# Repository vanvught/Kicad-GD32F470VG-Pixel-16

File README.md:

# Kicad GD32F470VG Pixel 16-ports x 4 Universes

Firmware [https://github.com/vanvught/GD32F470VG-Pixel-16-Ports](https://github.com/vanvught/GD32F470VG-Pixel-16-Ports)

More information [https://www.gd32-dmx.org/pixel.html](https://www.gd32-dmx.org/pixel.html)

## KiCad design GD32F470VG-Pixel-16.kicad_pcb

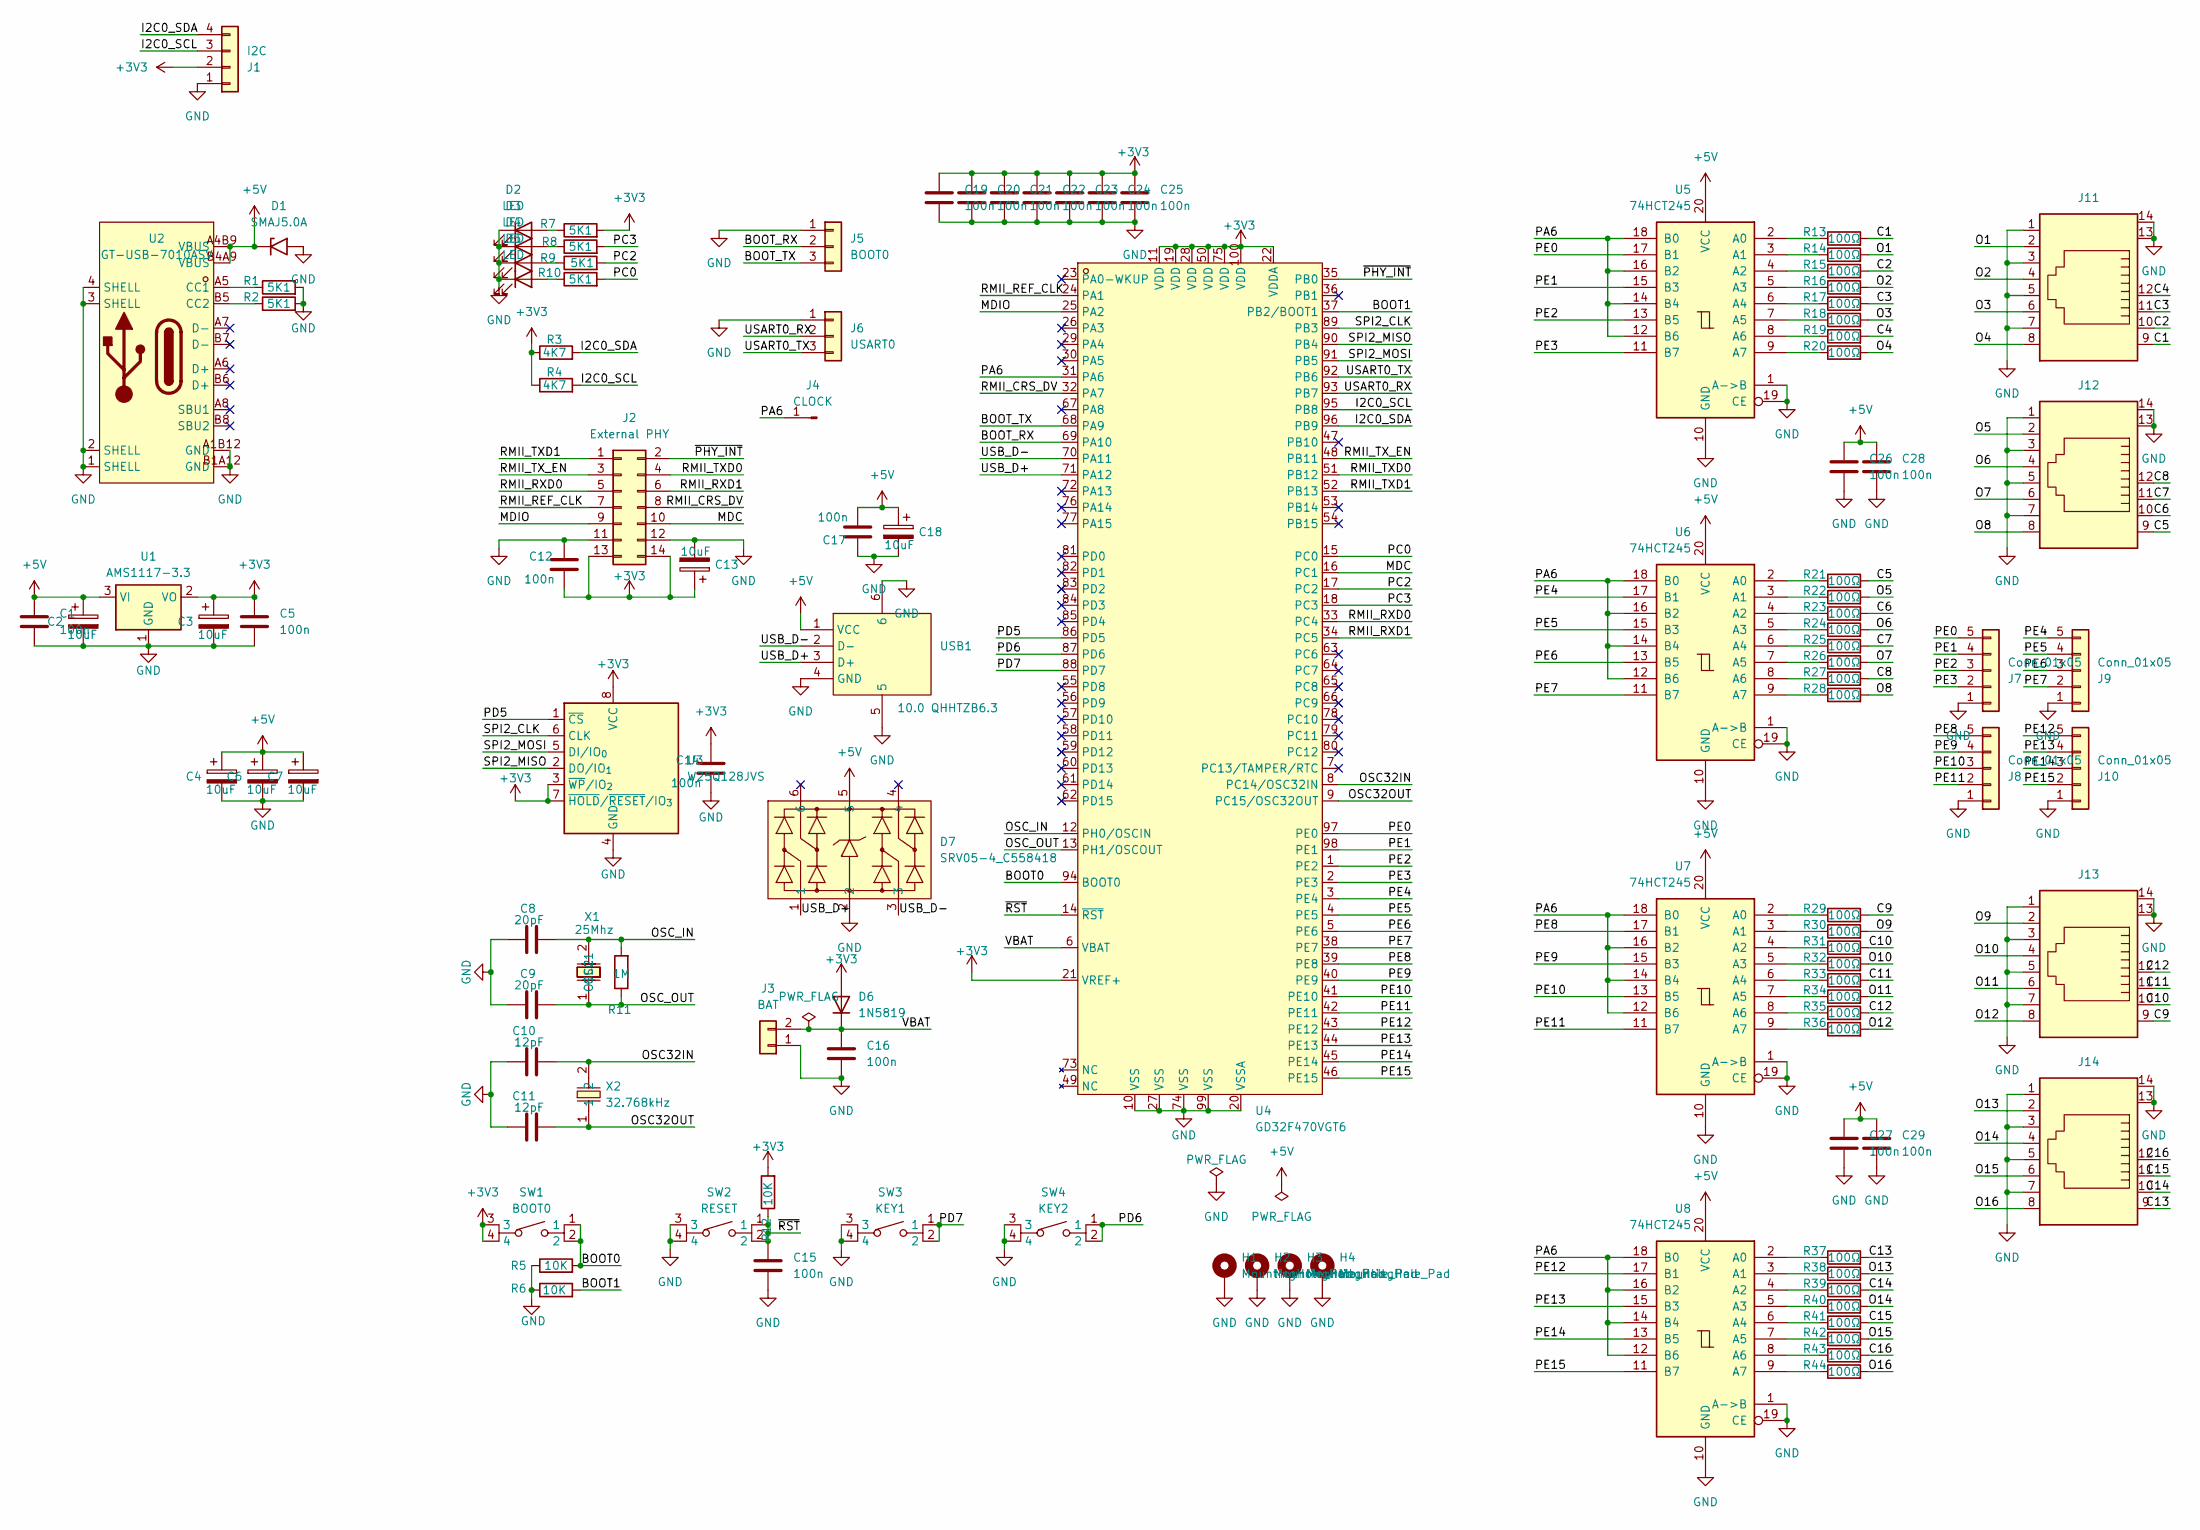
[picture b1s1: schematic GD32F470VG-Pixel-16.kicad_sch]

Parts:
C1, C5, C12, C14, C15, C16, C17, C19, C20, C21, C22, C23, C24, C25, C26, C27, C28, C29: 100n; C_0603_1608Metric; LCSC Part C14663
C2, C3, C4, C6, C7, C13, C18: 10uF; CP_EIA-3216-18_Kemet-A; LCSC Part C7171
C8, C9: 20pF; C_0603_1608Metric; LCSC Part C1648
C10, C11: 12pF; C_0603_1608Metric; LCSC Part C38523
D1: SMAJ5.0A; D_SMA; LCSC Part C113952
D2, D3, D4, D5: LED; LED_0805_2012Metric; LCSC Part C2297
D6: 1N5819; D_SOD-323; LCSC Part C48997863
D7: SRV05-4_C558418; SOT-23-6_L2.9-W1.6-P0.95-LS2.8-BL; MPN SRV05-4; LCSC Part C558418
H1, H2, H3, H4: MountingHole_Pad; MountingHole_2.7mm_M2.5_Pad
J1: I2C; PinHeader_1x04_P2.54mm_Vertical
J2: External PHY; PinSocket_2x07_P2.54mm_Horizontal
J3: BAT; PinHeader_1x02_P2.54mm_Vertical
J4: CLOCK; PinHeader_1x01_P2.54mm_Vertical
J5: BOOT0; PinHeader_1x03_P2.54mm_Vertical
J6: USART0; PinHeader_1x03_P2.54mm_Vertical
J7, J8, J9, J10: Conn_01x05; PinHeader_1x05_P2.54mm_Vertical
J11, J12, J13, J14: RJ45-with-additional-row
R1, R2, R7, R8, R9, R10: 5K1; R_0603_1608Metric; LCSC Part C23186
R3, R4: 4K7; R_0603_1608Metric; LCSC Part C23162
R5, R6, R12: 10K; R_0603_1608Metric; LCSC Part C25804
R11: 1M; R_0603_1608Metric; LCSC Part C22935
R13, R14, R15, R16, R17, R18, R19, R20, R21, R22, R23, R24, R25, R26, R27, R28, R29, R30, R31, R32, R33, R34, R35, R36, R37, R38, R39, R40, R41, R42, R43, R44: 100Ω; R_0603_1608Metric; LCSC Part C22775
SW1: BOOT0; KEY-SMD_4P-L6.0-W6.0-P4.50-LS9.0; MPN PTS645SM43SMTR92LFS; LCSC Part C221880
SW2: RESET; KEY-SMD_4P-L6.0-W6.0-P4.50-LS9.0; MPN PTS645SM43SMTR92LFS; LCSC Part C221880
SW3: KEY1; KEY-SMD_4P-L6.0-W6.0-P4.50-LS9.0; MPN PTS645SM43SMTR92LFS; LCSC Part C221880
SW4: KEY2; KEY-SMD_4P-L6.0-W6.0-P4.50-LS9.0; MPN PTS645SM43SMTR92LFS; LCSC Part C221880
U1: AMS1117-3.3; SOT-223-3_TabPin2
U2: GT-USB-7010ASV; USB-C-SMD_G-SWITCH_GT-USB-7010ASV; MPN GT-USB-7010ASV; LCSC Part C2988369
U3: W25Q128JVS; SOIC-8_5.3x5.3mm_P1.27mm; LCSC Part C97521
U4: GD32F470VGT6; LQFP-100_L14.0-W14.0-P0.50-LS16.0-BL; MPN GD32F470VGT6; LCSC Part C3029773
U5, U6, U7, U8: 74HCT245; SOIC-20W_7.5x12.8mm_P1.27mm; LCSC Part C5979
USB1: 10.0 QHHTZB6.3; USB-A-TH_10.0QHHTZB6.3; MPN 10.0 QHHTZB6.3; LCSC Part C668591
X1: 25Mhz; HC-49S_L11.4-W4.8; MPN X49SM25MSD2SC; LCSC Part C14872
X2: 32.768kHz; FC-135R_L3.2-W1.5; MPN Q13FC13500004; LCSC Part C32346

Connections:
+3V3: C3.1, C5.1, C12.2, C13.1, C14.1, C19.1, C20.1, C21.1, C22.1, C23.1, C24.1, C25.1, D6.2 (A), J1.2, J2.13, J2.14, R3.1, R4.1, R7.2, R12.2, SW1.3, SW1.4, U1.2 (VO), U3.3 (~WP/IO_{2}), U3.7 (~HOLD/~RESET/IO_{3}), U3.8 (VCC), U4.11 (VDD), U4.19 (VDD), U4.21 (VREF+), U4.22 (VDDA), U4.28 (VDD), U4.50 (VDD), U4.75 (VDD), U4.100 (VDD)
+5V: C1.1, C2.1, C4.1, C6.1, C7.1, C17.2, C18.1, C26.1, C27.1, C28.1, C29.1, D1.1 (A1), D7.5, U1.3 (VI), U2.A4B9 (VBUS), U2.B4A9 (VBUS), U5.20 (VCC), U6.20 (VCC), U7.20 (VCC), U8.20 (VCC), USB1.1 (VCC)
/BOOT0: R5.2, SW1.1, SW1.2, U4.94 (BOOT0)
/BOOT1: R6.2, U4.37 (PB2/BOOT1)
/BOOT_RX: J5.2, U4.69 (PA10)
/BOOT_TX: J5.3, U4.68 (PA9)
/C1: J11.9, R13.2
/C2: J11.10, R15.2
/C3: J11.11, R17.2
/C4: J11.12, R19.2
/C5: J12.9, R21.2
/C6: J12.10, R23.2
/C7: J12.11, R25.2
/C8: J12.12, R27.2
/C9: J13.9, R29.2
/C10: J13.10, R31.2
/C11: J13.11, R33.2
/C12: J13.12, R35.2
/C13: J14.9, R37.2
/C14: J14.10, R39.2
/C15: J14.11, R41.2
/C16: J14.12, R43.2
/I2C0_SCL: J1.3, R4.2, U4.95 (PB8)
/I2C0_SDA: J1.4, R3.2, U4.96 (PB9)
/MDC: J2.10, U4.16 (PC1)
/MDIO: J2.9, U4.25 (PA2)
/O1: J11.2, R14.2
/O2: J11.4, R16.2
/O3: J11.6, R18.2
/O4: J11.8, R20.2
/O5: J12.2, R22.2
/O6: J12.4, R24.2
/O7: J12.6, R26.2
/O8: J12.8, R28.2
/O9: J13.2, R30.2
/O10: J13.4, R32.2
/O11: J13.6, R34.2
/O12: J13.8, R36.2
/O13: J14.2, R38.2
/O14: J14.4, R40.2
/O15: J14.6, R42.2
/O16: J14.8, R44.2
/OSC32IN: C10.2, U4.8 (PC14/OSC32IN), X2.2
/OSC32OUT: C11.2, U4.9 (PC15/OSC32OUT), X2.1
/OSC_IN: C8.2, R11.2, U4.12 (PH0/OSCIN), X1.2 (OSC2)
/OSC_OUT: C9.2, R11.1, U4.13 (PH1/OSCOUT), X1.1 (OSC1)
/PA6: J4.1 (Pin_1_1), U4.31 (PA6), U5.12 (B6), U5.14 (B4), U5.16 (B2), U5.18 (B0), U6.12 (B6), U6.14 (B4), U6.16 (B2), U6.18 (B0), U7.12 (B6), U7.14 (B4), U7.16 (B2), U7.18 (B0), U8.12 (B6), U8.14 (B4), U8.16 (B2), U8.18 (B0)
/PC0: R10.2, U4.15 (PC0)
/PC2: R9.2, U4.17 (PC2)
/PC3: R8.2, U4.18 (PC3)
/PD5: U3.1 (~CS), U4.86 (PD5)
/PD6: SW4.1, SW4.2, U4.87 (PD6)
/PD7: SW3.1, SW3.2, U4.88 (PD7)
/PE0: J7.5, U4.97 (PE0), U5.17 (B1)
/PE1: J7.4, U4.98 (PE1), U5.15 (B3)
/PE2: J7.3, U4.1 (PE2), U5.13 (B5)
/PE3: J7.2, U4.2 (PE3), U5.11 (B7)
/PE4: J9.5, U4.3 (PE4), U6.17 (B1)
/PE5: J9.4, U4.4 (PE5), U6.15 (B3)
/PE6: J9.3, U4.5 (PE6), U6.13 (B5)
/PE7: J9.2, U4.38 (PE7), U6.11 (B7)
/PE8: J8.5, U4.39 (PE8), U7.17 (B1)
/PE9: J8.4, U4.40 (PE9), U7.15 (B3)
/PE10: J8.3, U4.41 (PE10), U7.13 (B5)
/PE11: J8.2, U4.42 (PE11), U7.11 (B7)
/PE12: J10.5, U4.43 (PE12), U8.17 (B1)
/PE13: J10.4, U4.44 (PE13), U8.15 (B3)
/PE14: J10.3, U4.45 (PE14), U8.13 (B5)
/PE15: J10.2, U4.46 (PE15), U8.11 (B7)
/RMII_CRS_DV: J2.8, U4.32 (PA7)
/RMII_REF_CLK: J2.7, U4.24 (PA1)
/RMII_RXD0: J2.5, U4.33 (PC4)
/RMII_RXD1: J2.6, U4.34 (PC5)
/RMII_TXD0: J2.4, U4.51 (PB12)
/RMII_TXD1: J2.1, U4.52 (PB13)
/RMII_TX_EN: J2.3, U4.48 (PB11)
/SPI2_CLK: U3.6 (CLK), U4.89 (PB3)
/SPI2_MISO: U3.2 (DO/IO_{1}), U4.90 (PB4)
/SPI2_MOSI: U3.5 (DI/IO_{0}), U4.91 (PB5)
/USART0_RX: J6.2, U4.93 (PB7)
/USART0_TX: J6.3, U4.92 (PB6)
/USB_D+: D7.1, U4.71 (PA12), USB1.3 (D+)
/USB_D-: D7.3, U4.70 (PA11), USB1.2 (D-)
/VBAT: C16.1, D6.1 (K), J3.2, U4.6 (VBAT)
/~PHY_INT: J2.2, U4.35 (PB0)
/~RST: C15.1, R12.1, SW2.1, SW2.2, U4.14 (~RST)
GND: C1.2, C2.2, C3.2, C4.2, C5.2, C6.2, C7.2, C8.1, C9.1, C10.1, C11.1, C12.1, C13.2, C14.2, C15.2, C16.2, C17.1, C18.2, C19.2, C20.2, C21.2, C22.2, C23.2, C24.2, C25.2, C26.2, C27.2, C28.2, C29.2, D1.2 (A2), D2.1 (K), D3.1 (K), D4.1 (K), D5.1 (K), D7.2, H1.1 (1_1), H2.1 (1_1), H3.1 (1_1), H4.1 (1_1), J1.1, J2.11, J2.12, J3.1, J5.1, J6.1, J7.1, J8.1, J9.1, J10.1, J11.1, J11.3, J11.5, J11.7, J11.13, J11.14, J12.1, J12.3, J12.5, J12.7, J12.13, J12.14, J13.1, J13.3, J13.5, J13.7, J13.13, J13.14, J14.1, J14.3, J14.5, J14.7, J14.13, J14.14, R1.2, R2.2, R5.1, R6.1, SW2.3, SW2.4, SW3.3, SW3.4, SW4.3, SW4.4, U1.1 (GND), U2.1 (SHELL), U2.2 (SHELL), U2.3 (SHELL), U2.4 (SHELL), U2.A1B12 (GND), U2.B1A12 (GND), U3.4 (GND), U4.10 (VSS), U4.20 (VSSA), U4.27 (VSS), U4.74 (VSS), U4.99 (VSS), U5.1 (A->B), U5.10 (GND), U5.19 (CE), U6.1 (A->B), U6.10 (GND), U6.19 (CE), U7.1 (A->B), U7.10 (GND), U7.19 (CE), U8.1 (A->B), U8.10 (GND), U8.19 (CE), USB1.4 (GND), USB1.5, USB1.6
unnamed: D2.2 (A), R7.1
unnamed: D3.2 (A), R8.1
unnamed: D4.2 (A), R9.1
unnamed: D5.2 (A), R10.1
unnamed: R1.1, U2.A5 (CC1)
unnamed: R2.1, U2.B5 (CC2)
unnamed: R13.1, U5.2 (A0)
unnamed: R14.1, U5.3 (A1)
unnamed: R15.1, U5.4 (A2)
unnamed: R16.1, U5.5 (A3)
unnamed: R17.1, U5.6 (A4)
unnamed: R18.1, U5.7 (A5)
unnamed: R19.1, U5.8 (A6)
unnamed: R20.1, U5.9 (A7)
unnamed: R21.1, U6.2 (A0)
unnamed: R22.1, U6.3 (A1)
unnamed: R23.1, U6.4 (A2)
unnamed: R24.1, U6.5 (A3)
unnamed: R25.1, U6.6 (A4)
unnamed: R26.1, U6.7 (A5)
unnamed: R27.1, U6.8 (A6)
unnamed: R28.1, U6.9 (A7)
unnamed: R29.1, U7.2 (A0)
unnamed: R30.1, U7.3 (A1)
unnamed: R31.1, U7.4 (A2)
unnamed: R32.1, U7.5 (A3)
unnamed: R33.1, U7.6 (A4)
unnamed: R34.1, U7.7 (A5)
unnamed: R35.1, U7.8 (A6)
unnamed: R36.1, U7.9 (A7)
unnamed: R37.1, U8.2 (A0)
unnamed: R38.1, U8.3 (A1)
unnamed: R39.1, U8.4 (A2)
unnamed: R40.1, U8.5 (A3)
unnamed: R41.1, U8.6 (A4)
unnamed: R42.1, U8.7 (A5)
unnamed: R43.1, U8.8 (A6)
unnamed: R44.1, U8.9 (A7)

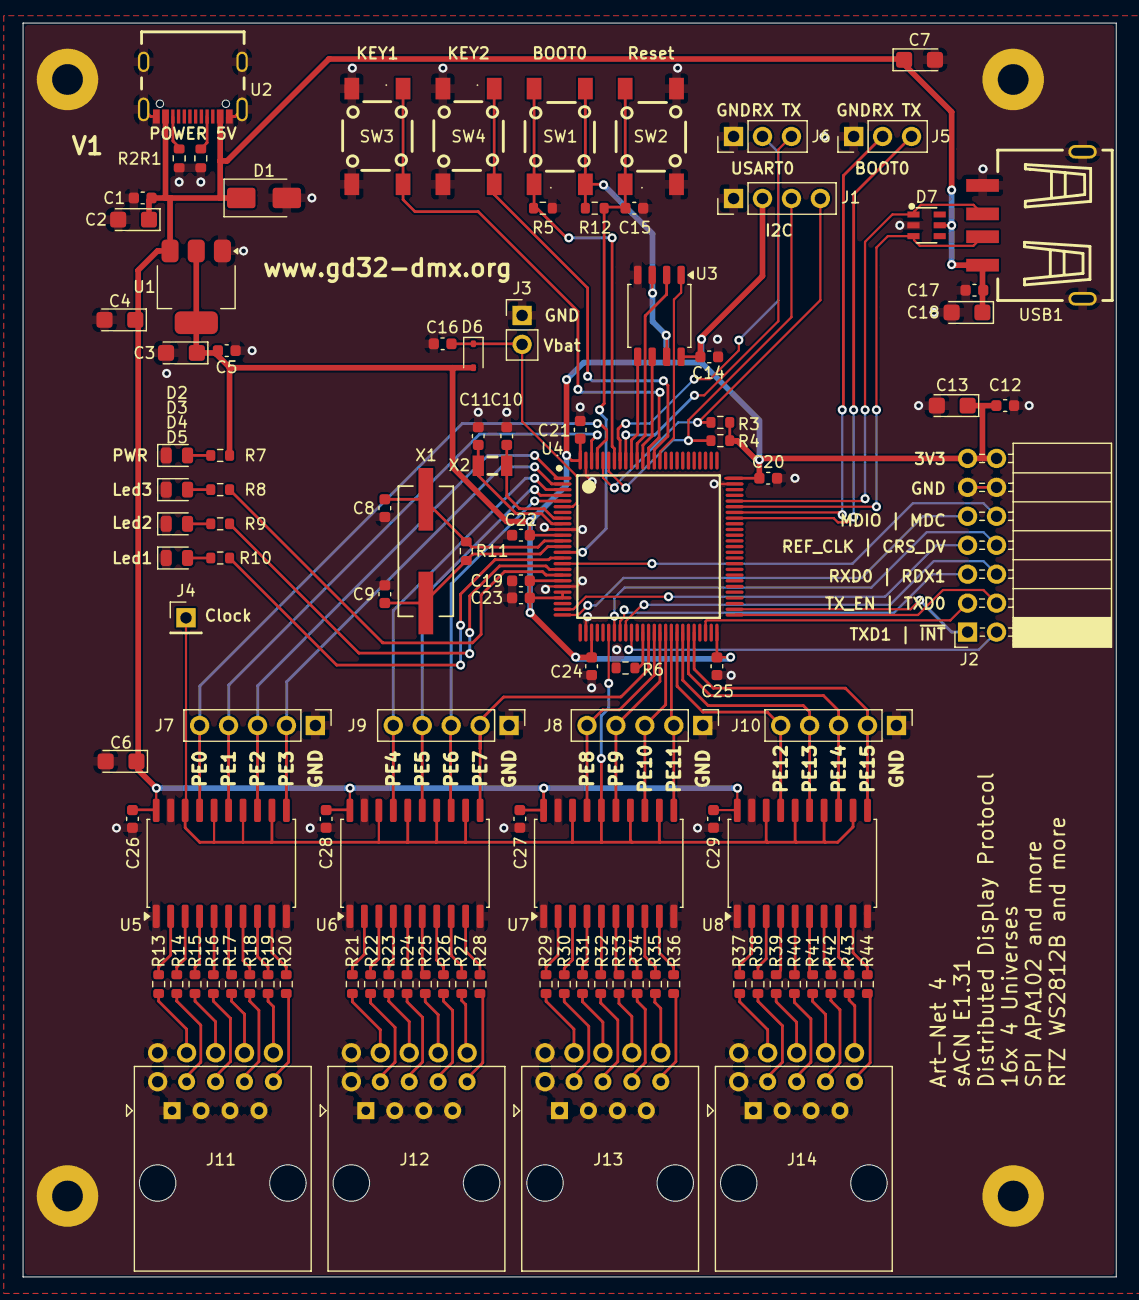
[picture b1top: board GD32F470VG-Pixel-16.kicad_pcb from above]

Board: 2 copper layers, 96.0 x 110.0 mm, 113 parts (0 on the bottom side), 125 nets.
